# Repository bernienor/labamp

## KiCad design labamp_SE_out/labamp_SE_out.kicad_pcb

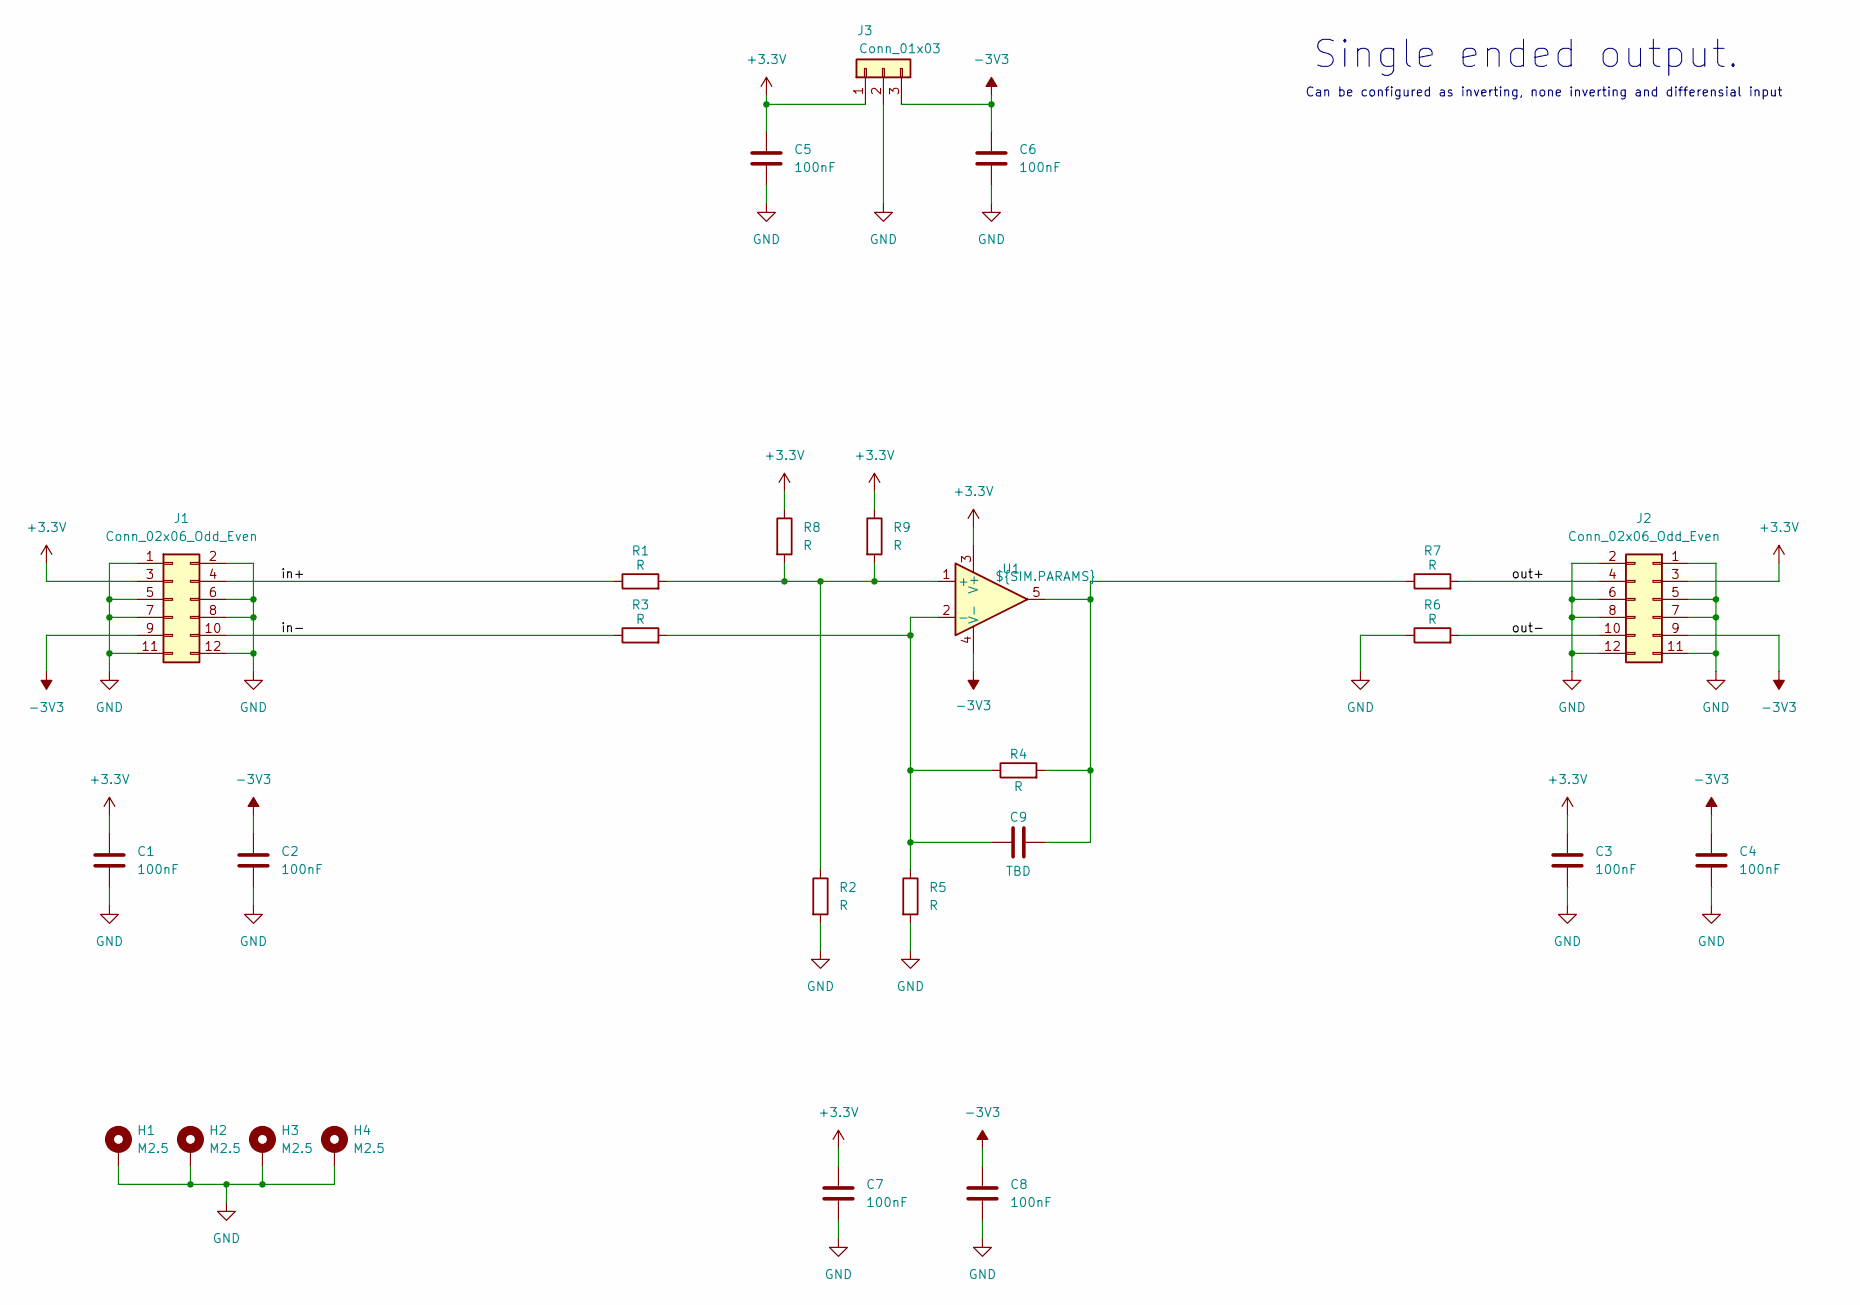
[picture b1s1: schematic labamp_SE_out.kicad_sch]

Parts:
C1, C2, C3, C4, C5, C6, C7, C8: 100nF; C_0603_1608Metric_Pad1.08x0.95mm_HandSolder
C9: TBD; C_0603_1608Metric_Pad1.08x0.95mm_HandSolder
H1, H2, H3, H4: M2.5; MountingHole_2.7mm_M2.5_ISO14580_Pad
J1, J2: Conn_02x06_Odd_Even; IDC12_edge
J3: Conn_01x03; PinHeader_1x03_P2.54mm_Vertical
R1, R2, R3, R4, R5, R6, R7, R8, R9: R; R_0603_1608Metric_Pad0.98x0.95mm_HandSolder
U1: ${SIM.PARAMS}; SOT-23-5

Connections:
+3.3V: C1.1, C3.1, C5.1, C7.1, J1.3, J2.3, J3.1, R8.1, R9.1, U1.3 (V+)
-3V3: C2.1, C4.1, C6.1, C8.1, J1.9, J2.9, J3.3, U1.4 (V-)
/in+: J1.4, R1.1
/in-: J1.10, R3.1
/out+: J2.4, R7.2
/out-: J2.10, R6.2
GND: C1.2, C2.2, C3.2, C4.2, C5.2, C6.2, C7.2, C8.2, H1.1, H2.1, H3.1, H4.1, J1.1, J1.2, J1.5, J1.6, J1.7, J1.8, J1.11, J1.12, J2.1, J2.2, J2.5, J2.6, J2.7, J2.8, J2.11, J2.12, J3.2, R2.2, R5.2, R6.1
unnamed: C9.2, R4.2, R7.1, U1.5
unnamed: R1.2, R2.1, R8.2, R9.2, U1.1 (+)
unnamed: C9.1, R3.2, R4.1, R5.1, U1.2 (-)

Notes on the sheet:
Single ended output.
Can be configured as inverting, none inverting and differensial input

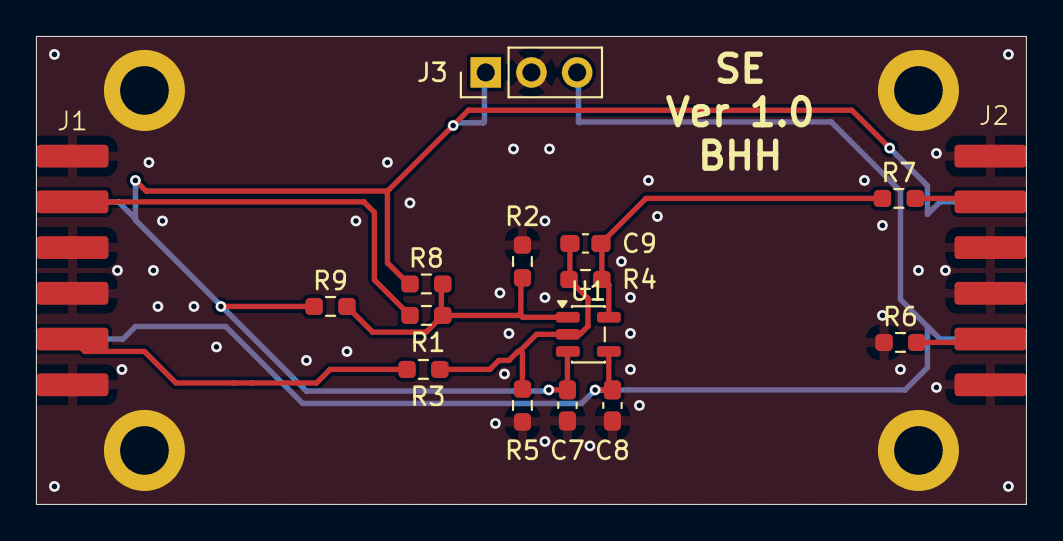
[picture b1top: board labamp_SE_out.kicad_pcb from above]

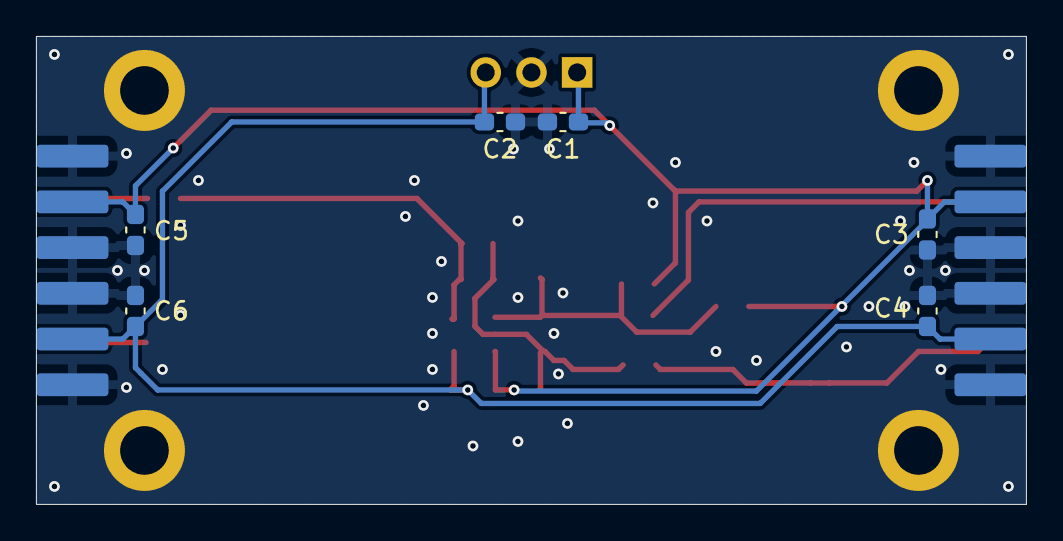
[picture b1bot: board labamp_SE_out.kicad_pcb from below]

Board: 2 copper layers, 55.0 x 26.0 mm, 26 parts (8 on the bottom side), 10 nets.

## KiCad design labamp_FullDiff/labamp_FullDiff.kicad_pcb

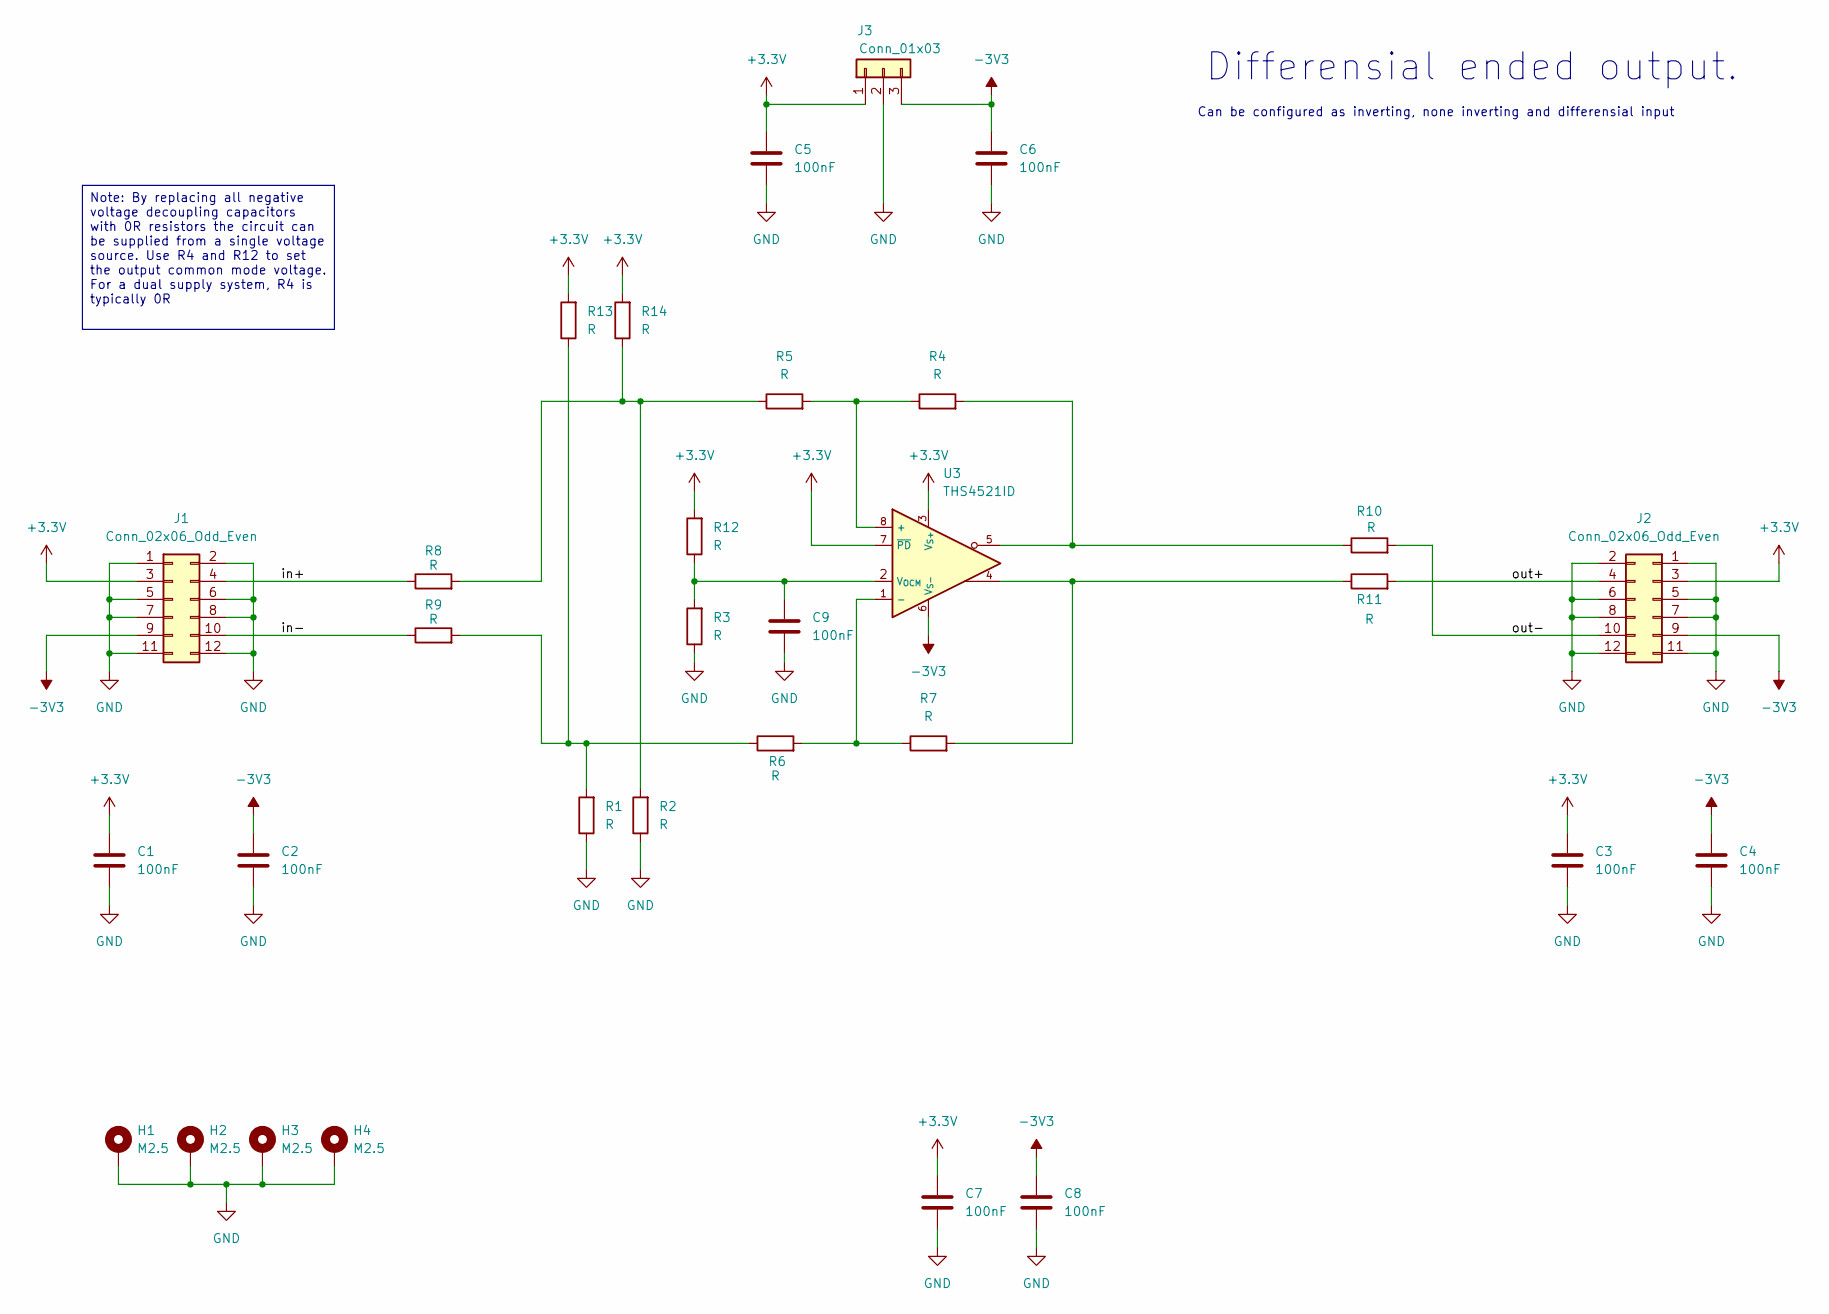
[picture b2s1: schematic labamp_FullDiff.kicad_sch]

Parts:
C1, C2, C3, C4, C5, C6, C7, C8, C9: 100nF; C_0603_1608Metric_Pad1.08x0.95mm_HandSolder
H1, H2, H3, H4: M2.5; MountingHole_2.7mm_M2.5_ISO14580_Pad
J1, J2: Conn_02x06_Odd_Even; IDC12_edge
J3: Conn_01x03; PinHeader_1x03_P2.54mm_Vertical
R1, R2, R3, R4, R5, R6, R7, R8, R9, R10, R11, R12, R13, R14: R; R_0603_1608Metric_Pad0.98x0.95mm_HandSolder
U3: THS4521ID; SOIC-8_3.9x4.9mm_P1.27mm

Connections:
+3.3V: C1.1, C3.1, C5.1, C7.1, J1.3, J2.3, J3.1, R12.2, R13.2, R14.2, U3.3 (V_{S+}), U3.7 (~PD)
-3V3: C2.1, C4.1, C6.1, C8.1, J1.9, J2.9, J3.3, U3.6 (V_{S-})
/in+: J1.4, R8.1
/in-: J1.10, R9.1
/out+: J2.4, R11.2
/out-: J2.10, R10.2
GND: C1.2, C2.2, C3.2, C4.2, C5.2, C6.2, C7.2, C8.2, C9.2, H1.1, H2.1, H3.1, H4.1, J1.1, J1.2, J1.5, J1.6, J1.7, J1.8, J1.11, J1.12, J2.1, J2.2, J2.5, J2.6, J2.7, J2.8, J2.11, J2.12, J3.2, R1.1, R2.1, R3.1
unnamed: R1.2, R6.1, R9.2, R13.1
unnamed: R4.2, R10.1, U3.5
unnamed: R7.2, R11.1, U3.4
unnamed: R2.2, R5.1, R8.2, R14.1
unnamed: R4.1, R5.2, U3.8 (+)
unnamed: R6.2, R7.1, U3.1 (-)
unnamed: C9.1, R3.2, R12.1, U3.2 (V_{OCM})

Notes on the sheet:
Can be configured as inverting, none inverting and differensial input
Differensial ended output.
Note: By replacing all negative voltage decoupling capacitors with 0R resistors the circuit can be supplied from a single voltage source. Use R4 and R12 to set the output common mode voltage. For a dual supply system, R4 is typically 0R

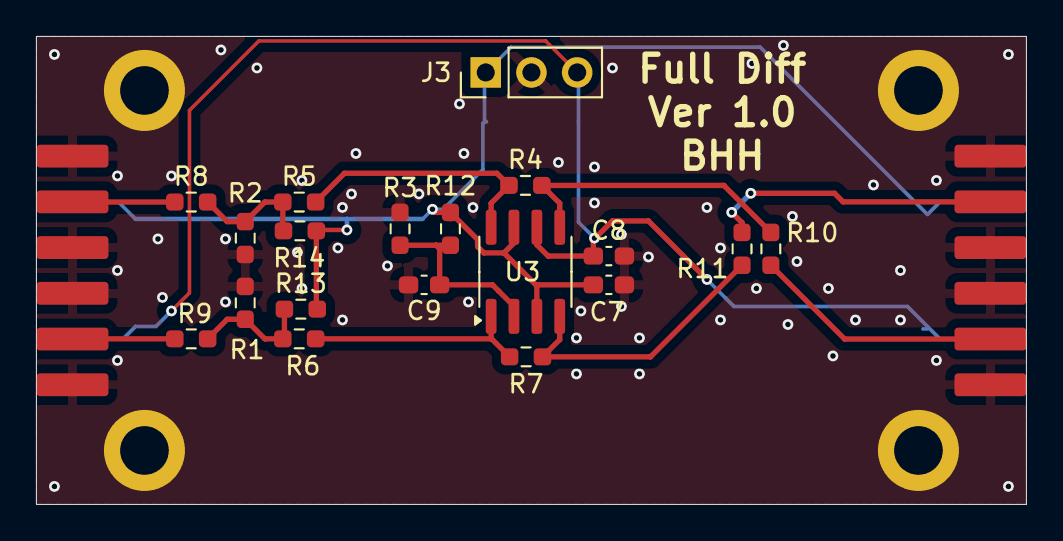
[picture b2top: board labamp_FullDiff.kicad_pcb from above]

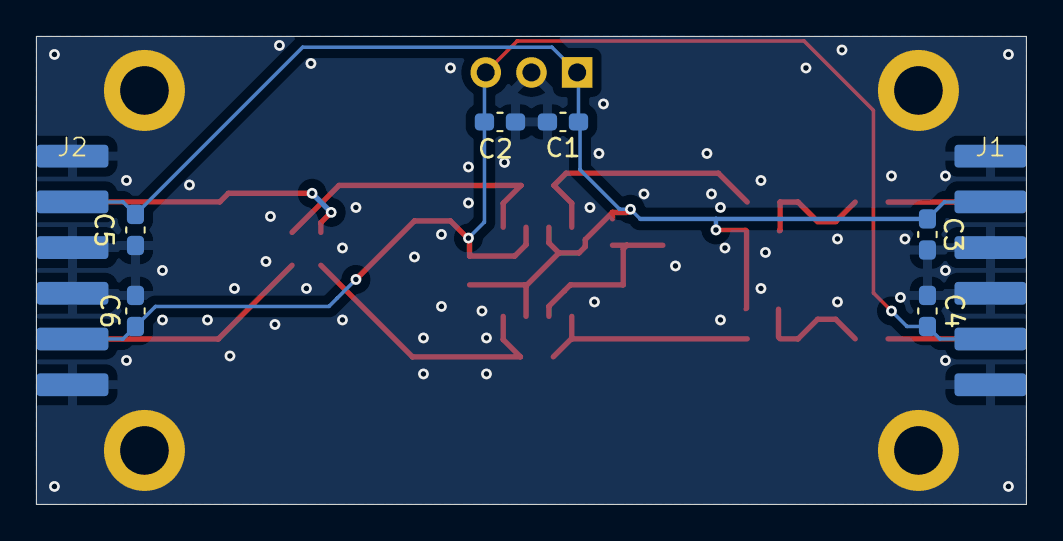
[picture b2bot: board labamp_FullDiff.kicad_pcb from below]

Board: 2 copper layers, 55.0 x 26.0 mm, 31 parts (8 on the bottom side), 14 nets.

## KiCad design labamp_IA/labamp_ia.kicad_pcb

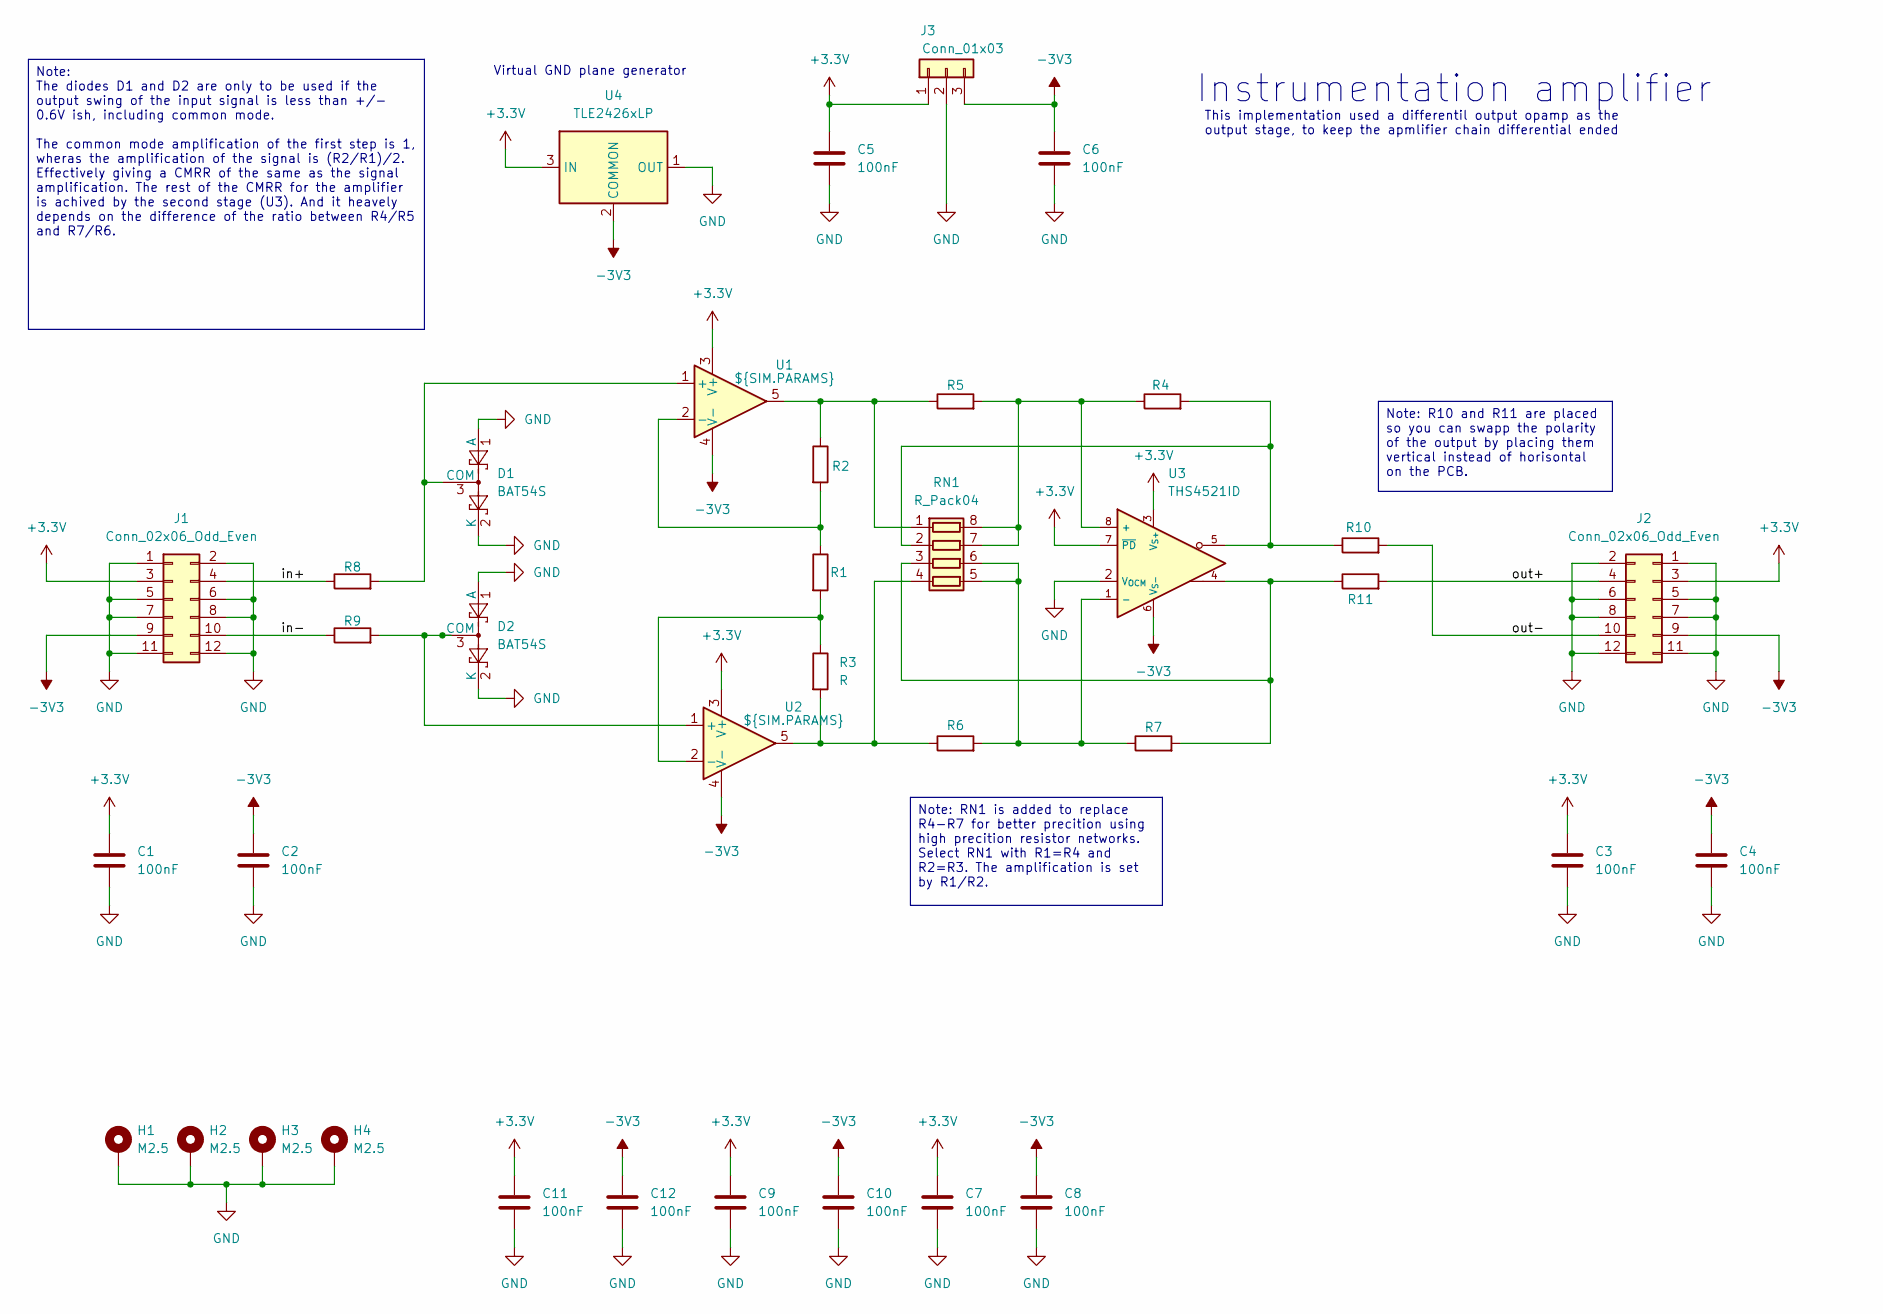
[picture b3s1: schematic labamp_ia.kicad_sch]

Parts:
C1, C2, C3, C4, C5, C6, C7, C8, C9, C10, C11, C12: 100nF; C_0603_1608Metric_Pad1.08x0.95mm_HandSolder
D1, D2: BAT54S; SOT-23
H1, H2, H3, H4: M2.5; MountingHole_2.7mm_M2.5_ISO14580_Pad
J1, J2: Conn_02x06_Odd_Even; IDC12_edge
J3: Conn_01x03; PinHeader_1x03_P2.54mm_Vertical
R1, R2, R3, R4, R5, R6, R7, R8, R9, R10, R11: R; R_0603_1608Metric_Pad0.98x0.95mm_HandSolder
RN1: R_Pack04; R_Array_Concave_4x0603
U1, U2: ${SIM.PARAMS}; SOT-23-5
U3: THS4521ID; SOIC-8_3.9x4.9mm_P1.27mm
U4: TLE2426xLP; TO-92_Inline

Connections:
+3.3V: C1.1, C3.1, C5.1, C7.1, C9.1, C11.1, J1.3, J2.3, J3.1, U1.3 (V+), U2.3 (V+), U3.3 (V_{S+}), U3.7 (~PD), U4.3 (IN)
-3V3: C2.1, C4.1, C6.1, C8.1, C10.1, C12.1, J1.9, J2.9, J3.3, U1.4 (V-), U2.4 (V-), U3.6 (V_{S-}), U4.2 (COMMON)
/in+: J1.4, R8.1
/in-: J1.10, R9.1
/out+: J2.4, R11.2
/out-: J2.10, R10.2
GND: C1.2, C2.2, C3.2, C4.2, C5.2, C6.2, C7.2, C8.2, C9.2, C10.2, C11.2, C12.2, D1.1 (A), D1.2 (K), D2.1 (A), D2.2 (K), H1.1, H2.1, H3.1, H4.1, J1.1, J1.2, J1.5, J1.6, J1.7, J1.8, J1.11, J1.12, J2.1, J2.2, J2.5, J2.6, J2.7, J2.8, J2.11, J2.12, J3.2, U3.2 (V_{OCM}), U4.1 (OUT)
unnamed: D1.3 (COM), R8.2, U1.1 (+)
unnamed: D2.3 (COM), R9.2, U2.1 (+)
unnamed: R2.1, R5.1, RN1.1 (R1.1), U1.5
unnamed: R4.1, R5.2, RN1.7 (R2.2), RN1.8 (R1.2), U3.8 (+)
unnamed: R4.2, R10.1, RN1.2 (R2.1), U3.5
unnamed: R7.2, R11.1, RN1.3 (R3.1), U3.4
unnamed: R6.2, R7.1, RN1.5 (R4.2), RN1.6 (R3.2), U3.1 (-)
unnamed: R3.2, R6.1, RN1.4 (R4.1), U2.5
unnamed: R1.1, R2.2, U1.2 (-)
unnamed: R1.2, R3.1, U2.2 (-)

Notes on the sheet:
Virtual GND plane generator
This implementation used a differentil output opamp as the output stage, to keep the apmlifier chain differential ended
Instrumentation amplifier
Note: R10 and R11 are placed so you can swapp the polarity of the output by placing them vertical instead of horisontal on the PCB.
Note: The diodes D1 and D2 are only to be used if the output swing of the input signal is less than +/- 0.6V ish, including common mode. The common mode amplification of the first step is 1, wheras the amplification of the signal is (R2/R1)/2. Effectively giving a CMRR of the same as the signal amp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
Note: RN1 is added to replace R4-R7 for better precition using high precition resistor networks. Select RN1 with R1=R4 and R2=R3. The amplification is set by R1/R2.

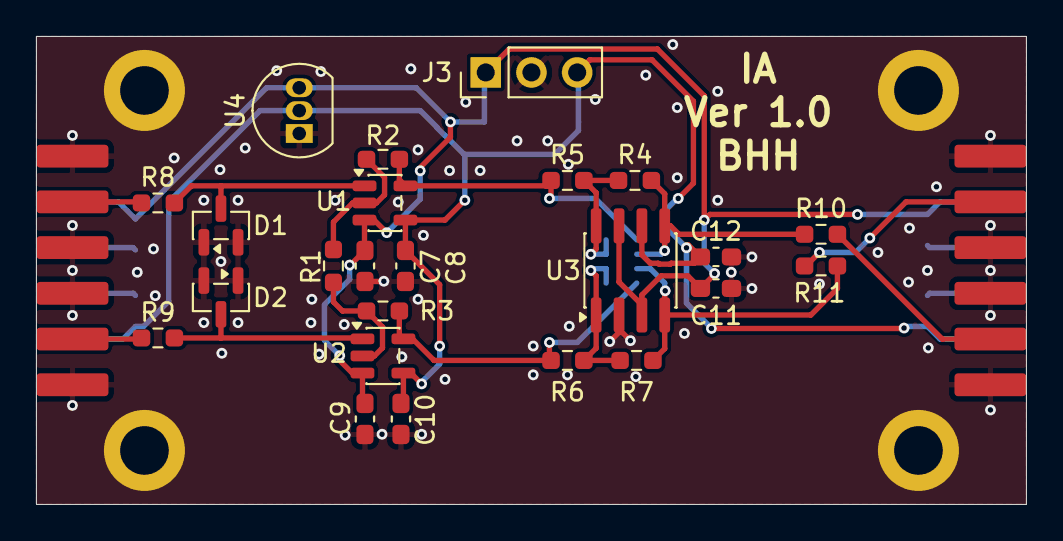
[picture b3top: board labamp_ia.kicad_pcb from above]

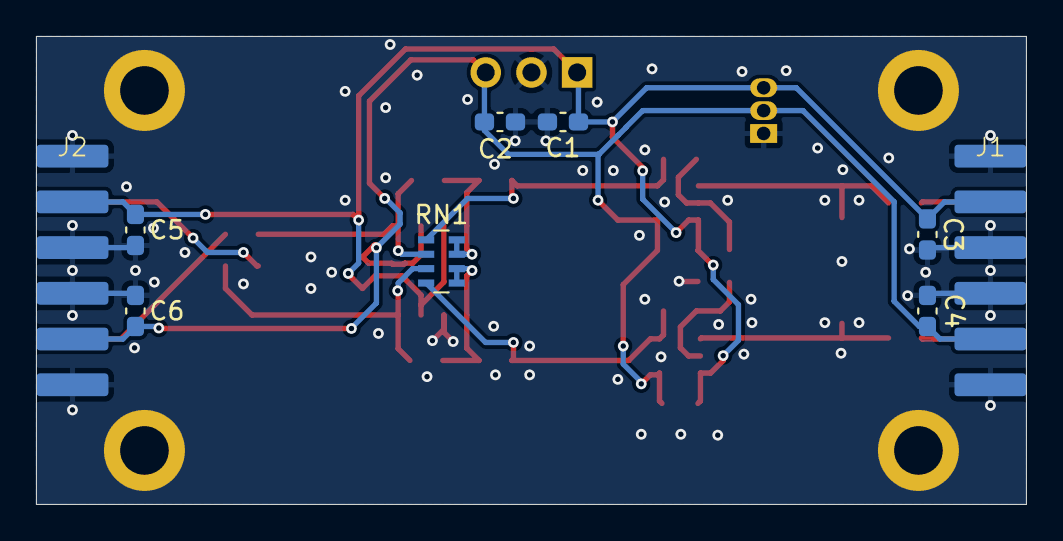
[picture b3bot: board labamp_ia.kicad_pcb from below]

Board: 2 copper layers, 55.0 x 26.0 mm, 37 parts (9 on the bottom side), 17 nets.

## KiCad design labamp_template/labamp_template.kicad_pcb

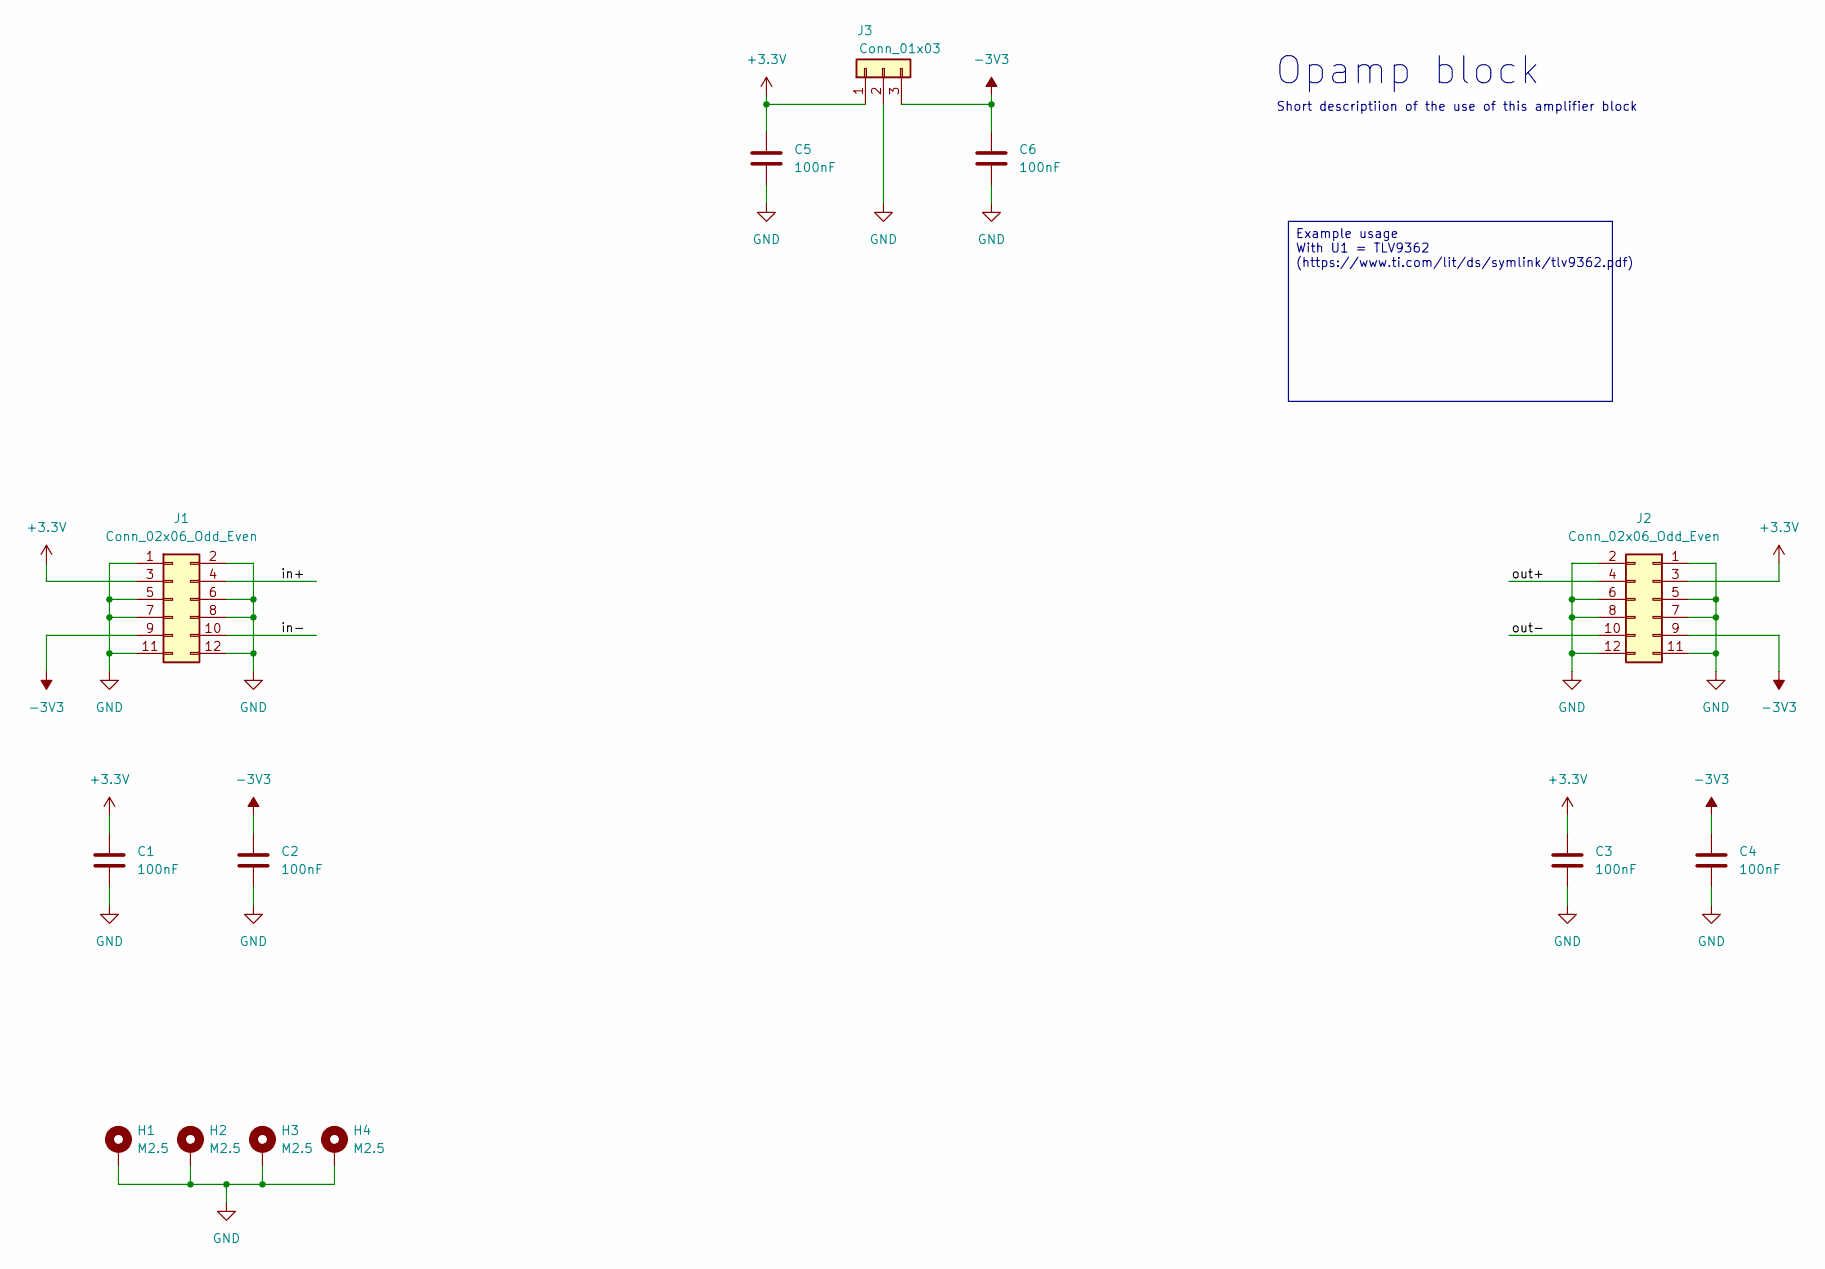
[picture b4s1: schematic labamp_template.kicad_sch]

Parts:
C1, C2, C3, C4, C5, C6: 100nF; C_0603_1608Metric_Pad1.08x0.95mm_HandSolder
H1, H2, H3, H4: M2.5; MountingHole_2.7mm_M2.5_ISO14580_Pad
J1, J2: Conn_02x06_Odd_Even; IDC12_edge
J3: Conn_01x03; PinHeader_1x03_P2.54mm_Vertical

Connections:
+3.3V: C1.1, C3.1, C5.1, J1.3, J2.3, J3.1
-3V3: C2.1, C4.1, C6.1, J1.9, J2.9, J3.3
/in+: J1.4
/in-: J1.10
/out+: J2.4
/out-: J2.10
GND: C1.2, C2.2, C3.2, C4.2, C5.2, C6.2, H1.1, H2.1, H3.1, H4.1, J1.1, J1.2, J1.5, J1.6, J1.7, J1.8, J1.11, J1.12, J2.1, J2.2, J2.5, J2.6, J2.7, J2.8, J2.11, J2.12, J3.2

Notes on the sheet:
Opamp block
Short descriptiion of the use of this amplifier block
Example usage With U1 = TLV9362 (https://www.ti.com/lit/ds/symlink/tlv9362.pdf)

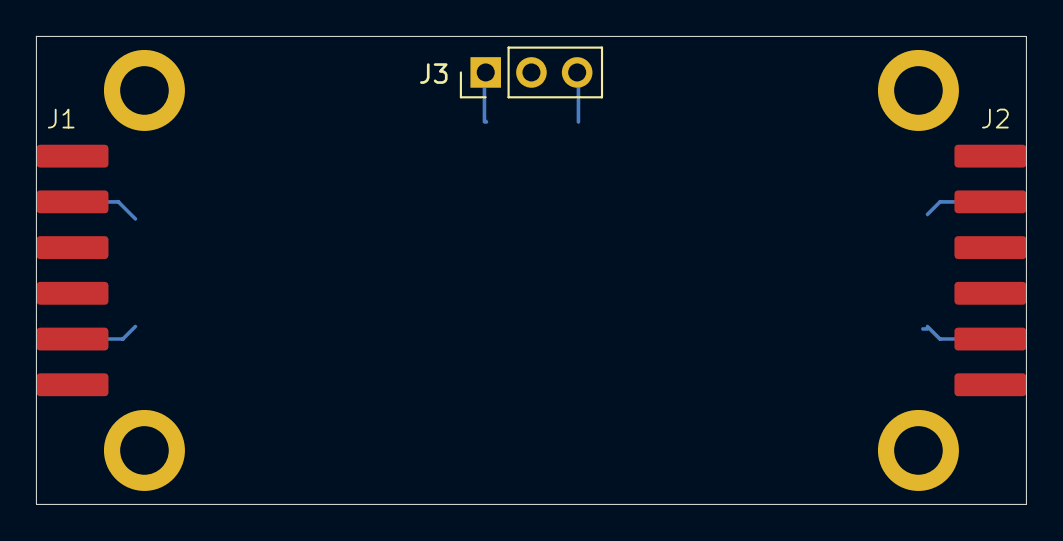
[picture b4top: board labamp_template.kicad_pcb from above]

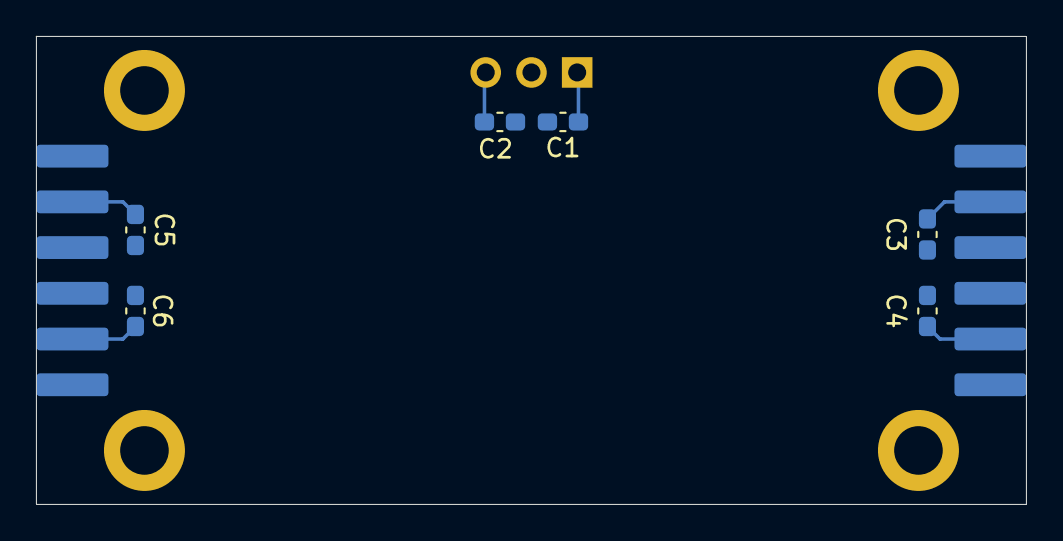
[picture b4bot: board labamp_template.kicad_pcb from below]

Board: 2 copper layers, 55.0 x 26.0 mm, 13 parts (8 on the bottom side), 3 nets.

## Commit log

2025-12-10 Initial commit of templates for schematics and PCBs
2025-12-14 Copied templates to Instrument Amplifier project
2026-01-14 Added instrument amplificer schematics
2026-01-16 Added files for Single Ended filter, copy of template
2026-01-16 Updated SE filter schematics
2026-01-17 Added Schematic for Single ended output amplifier
2026-01-17 Added output resistors to instrument amplifier schematics
2026-01-17 Added output resistors to Single ended filter schematics
2026-01-17 Added resistors to unused out- net to gnd
2026-01-17 Added title and subtitle to schematics template
2026-01-17 Routed Single ended output PCB
2026-01-17 Added notes and info to Instrument Amplifiser Schematics
2026-01-17 Added Fully differentioal amplification stage
2026-01-18 Routed PCB for IA. Added resistor network for high precition resistors.
2026-01-18 Minor corrections.
2026-01-20 Adjusted component labeling in silkscreen
2026-01-23 PCB layout od Diff ampl started
2026-01-23 .gitignore added
2026-01-23 Deleted a .kicad_prl file
2026-01-31 Added option for single supply
2026-02-04 Updated template PCB layout rules
2026-03-03 Added pullup resistors on inputs
2026-03-03 Moved mounting holes to avoid colision with header
2026-03-06 Added virtual GND plane generator to IA
2026-03-07 Finished FullDiff routing. PCB rules updated
2026-03-07 SE filter routed 90%
2026-03-07 Finished routing
2026-03-07 Finished routing SE_out
2026-03-07 Cleaned up silkscreen IA
2026-03-08 Missing file from last commit
2026-03-08 Fixed H1-H4 in silkscreen
2026-03-08 Addedversion etc. in silkscreen
2026-03-09 Added fabrication files for version 1.0 of all boards
